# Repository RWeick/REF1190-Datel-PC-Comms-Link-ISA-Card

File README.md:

# REF1190-Datel-PC-Comms-Link-ISA-Card
Everything necessary to produce and use the PC Comms Link ISA Card for use with the PSX, N64, and Saturn cheat devices.

This card was designed for use with the original PSX Gameshark / Action Replay, the Sega Saturn Gameshark / Action Replay, and the [N64 Cheat Development System](https://www.nesworld.com/n64-dateltrainercart.php).

PCB Thickness: 1.6 mm

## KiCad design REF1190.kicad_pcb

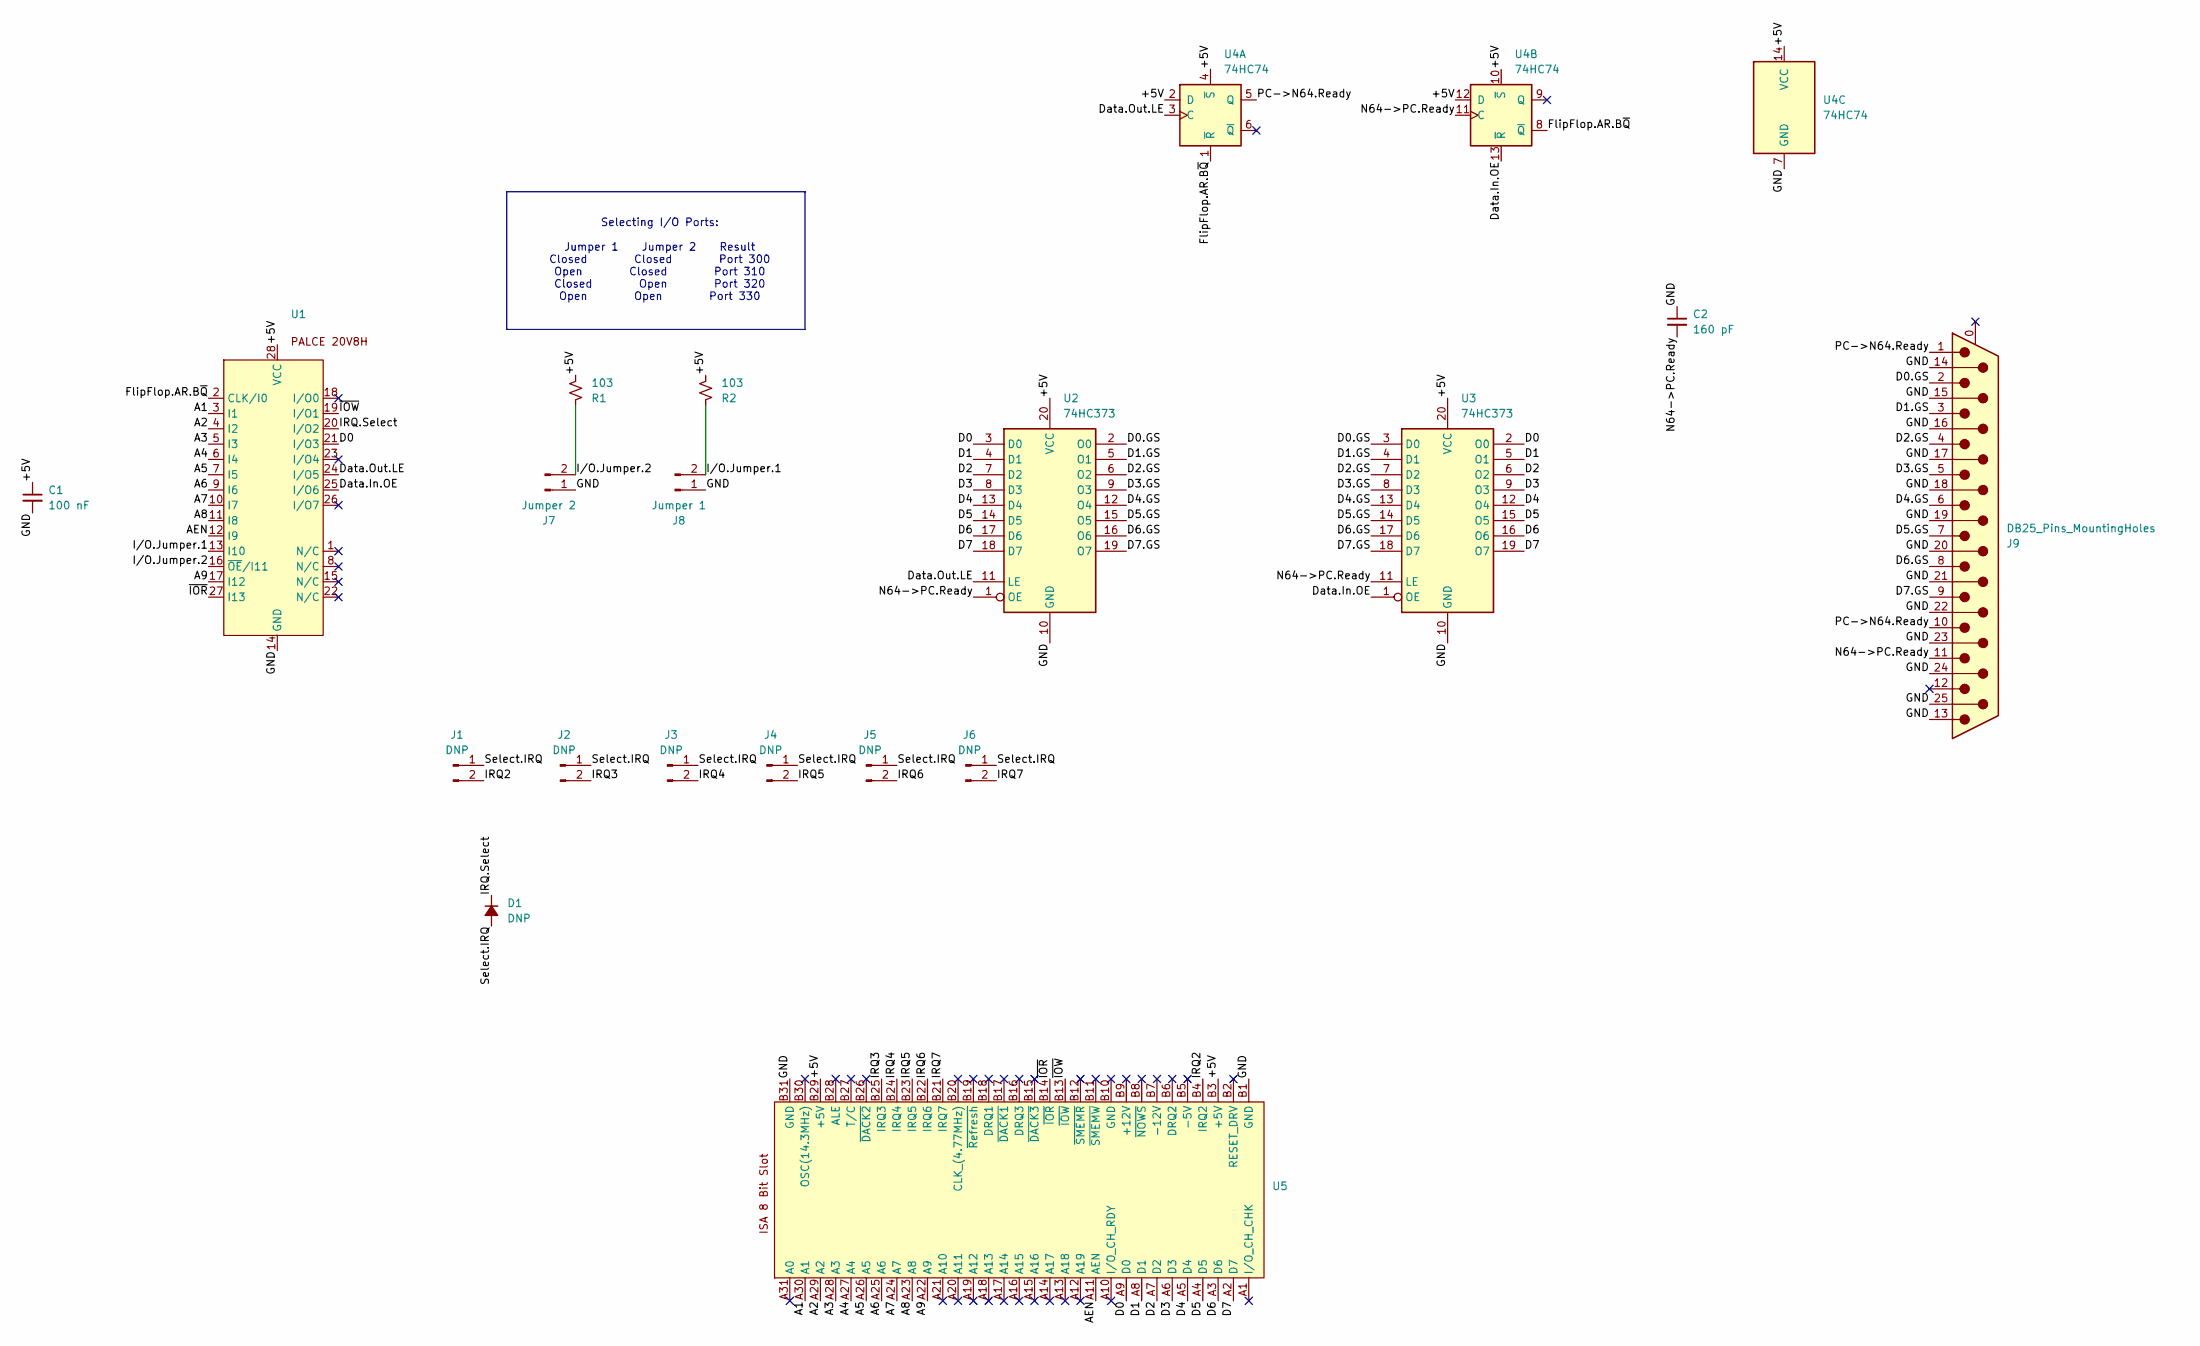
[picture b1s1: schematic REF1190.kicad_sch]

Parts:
C1: 100 nF; SMD
C2: 160 pF; SMD
D1: DNP
J1, J2, J3, J4, J5, J6: DNP; Jumper
J7: Jumper 2; Jumper
J8: Jumper 1; Jumper
J9: DB25_Pins_MountingHoles; DSUB-25_Socket_Vertical_P2.77x2.84mm_MountingHoles
R1, R2: 103; SMD
U1: PLCC-28
U2, U3: 74HC373; SOIC-20
U4: 74HC74; SOIC-14
U5: ISA Edge Connector

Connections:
/+5V: C1.1, R1.2, R2.2, U1.28 (VCC), U2.20 (VCC), U3.20 (VCC), U4.2 (D), U4.4 (~S), U4.10 (~S), U4.12 (D), U4.14 (VCC), U5.B3 (+5V), U5.B29 (+5V)
/A1: U1.3 (I1), U5.A30 (A1)
/A2: U1.4 (I2), U5.A29 (A2)
/A3: U1.5 (I3), U5.A28 (A3)
/A4: U1.6 (I4), U5.A27 (A4)
/A5: U1.7 (I5), U5.A26 (A5)
/A6: U1.9 (I6), U5.A25 (A6)
/A7: U1.10 (I7), U5.A24 (A7)
/A8: U1.11 (I8), U5.A23 (A8)
/A9: U1.17 (I12), U5.A22 (A9)
/AEN: U1.12 (I9), U5.A11 (AEN)
/D0: U1.21 (I/O3), U2.3 (D0), U3.2 (O0), U5.A9 (D0)
/D0.GS: J9.2, U2.2 (O0), U3.3 (D0)
/D1: U2.4 (D1), U3.5 (O1), U5.A8 (D1)
/D1.GS: J9.3, U2.5 (O1), U3.4 (D1)
/D2: U2.7 (D2), U3.6 (O2), U5.A7 (D2)
/D2.GS: J9.4, U2.6 (O2), U3.7 (D2)
/D3: U2.8 (D3), U3.9 (O3), U5.A6 (D3)
/D3.GS: J9.5, U2.9 (O3), U3.8 (D3)
/D4: U2.13 (D4), U3.12 (O4), U5.A5 (D4)
/D4.GS: J9.6, U2.12 (O4), U3.13 (D4)
/D5: U2.14 (D5), U3.15 (O5), U5.A4 (D5)
/D5.GS: J9.7, U2.15 (O5), U3.14 (D5)
/D6: U2.17 (D6), U3.16 (O6), U5.A3 (D6)
/D6.GS: J9.8, U2.16 (O6), U3.17 (D6)
/D7: U2.18 (D7), U3.19 (O7), U5.A2 (D7)
/D7.GS: J9.9, U2.19 (O7), U3.18 (D7)
/Data.In.OE: U1.25 (I/O6), U3.1 (OE), U4.13 (~R)
/Data.Out.LE: U1.24 (I/O5), U2.11 (LE), U4.3 (C)
/FlipFlop1.Q: J9.1, J9.10, U4.5 (Q)
/FlipFlop.AR.B~Q: U1.2 (CLK/I0), U4.1 (~R), U4.8 (~Q)
/GND: C1.2, C2.1, J7.1, J8.1, J9.13, J9.14, J9.15, J9.16, J9.17, J9.18, J9.19, J9.20, J9.21, J9.22, J9.23, J9.24, J9.25, U1.14 (GND), U2.10 (GND), U3.10 (GND), U4.7 (GND), U5.B1 (GND), U5.B31 (GND)
/IRQ2: J1.2, U5.B4 (IRQ2)
/IRQ3: J2.2, U5.B25 (IRQ3)
/IRQ4: J3.2, U5.B24 (IRQ4)
/IRQ5: J4.2, U5.B23 (IRQ5)
/IRQ6: J5.2, U5.B22 (IRQ6)
/IRQ7: J6.2, U5.B21 (IRQ7)
/IRQ.Select: D1.1 (K), U1.20 (I/O2)
/I/O.Jumper.1: J8.2, R2.1, U1.13 (I10)
/I/O.Jumper.2: J7.2, R1.1, U1.16 (~OE/I11)
/Latch1.OE.2LE: C2.2, J9.11, U2.1 (OE), U3.11 (LE), U4.11 (C)
/Select.IRQ: D1.2 (A), J1.1, J2.1, J3.1, J4.1, J5.1, J6.1
/~IOR: U1.27 (I13), U5.B14 (~IOR)
/~IOW: U1.19 (I/O1), U5.B13 (~IOW)

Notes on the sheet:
Selecting I/O Ports: Jumper 1 Jumper 2 Result Closed Closed Port 300 Open Closed Port 310 Closed Open Port 320 Open Open Port 330

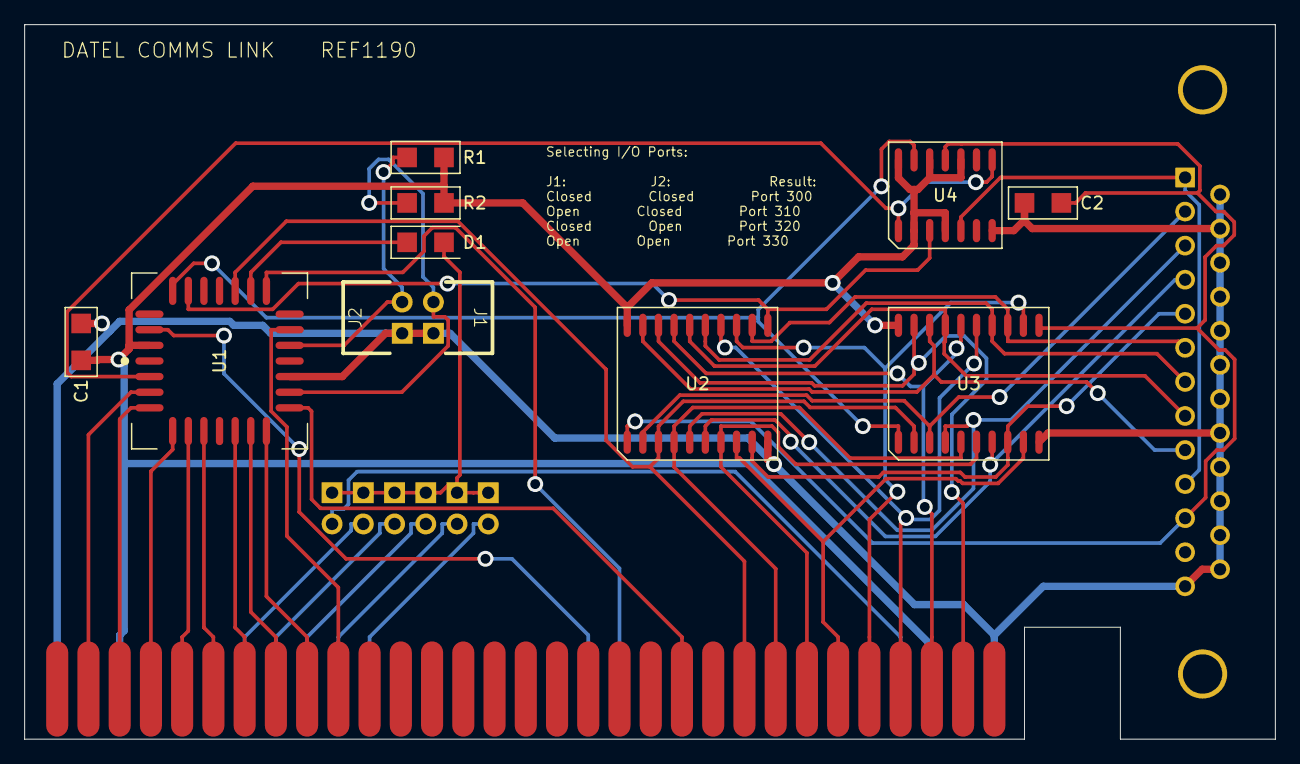
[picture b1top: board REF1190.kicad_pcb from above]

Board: 2 copper layers, 101.7 x 58.1 mm, 19 parts (0 on the bottom side), 45 nets.
